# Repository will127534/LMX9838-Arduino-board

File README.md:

# LMX9838-Arduino-board
An Arduino leonardo board with LMX9838 BT2.0 module

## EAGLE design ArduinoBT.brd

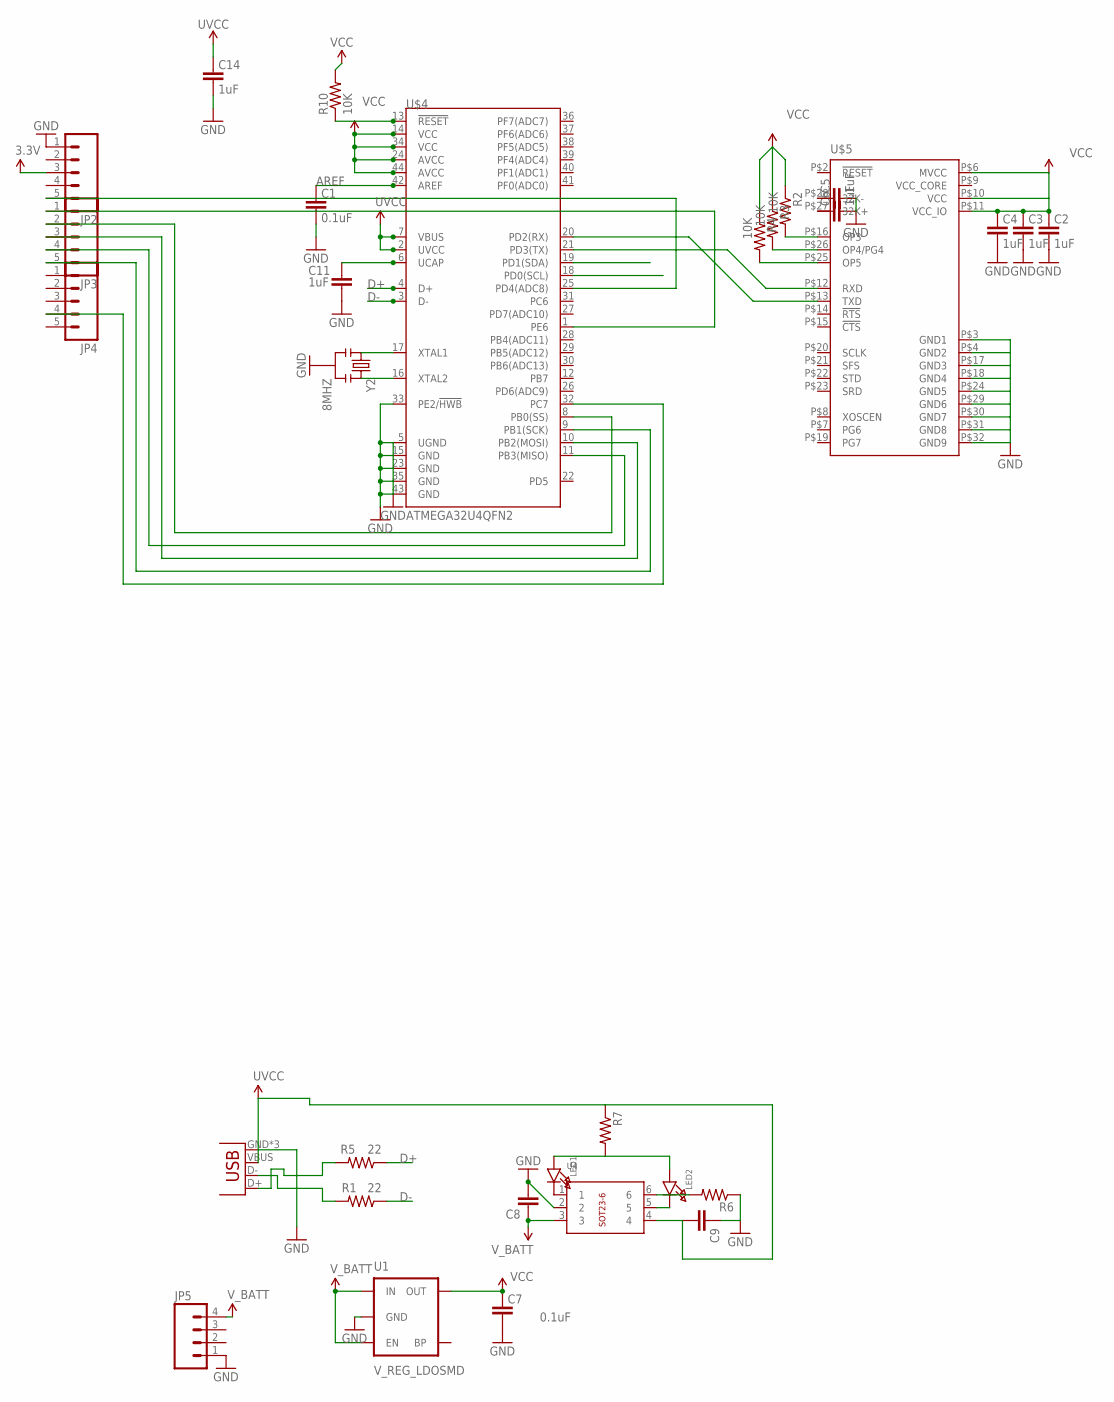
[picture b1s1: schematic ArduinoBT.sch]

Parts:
C1, C7: 0.1uF; 0603-CAP
C2, C3, C4, C5, C6, C11, C14: 1uF; 0603-CAP
C8, C9: CAP0805; 0805
JP1: USB-MICROB
JP2, JP3, JP4: M051.27MM; 1X05-1.27MM
JP5: M041.27MM; 1X04-1.27MM
LED1, LED2: LED0603_NOOUTLINE; CHIPLED_0603_NOOUTLINE
R1, R5: 22; 0603-RES
R2, R3, R4, R10: 10K; 0603-RES
R6, R7: RESISTOR0805-RES; 0805
U1: V_REG_LDOSMD; SOT23-5
U4: BREAKOUT_SOT23-6
U$4: ATMEGA32U4QFN2; SPARKFUN-DIGITALIC_QFN-44-NOPAD
U$5: LMX9838; LTCC70
Y2: 8MHZ; RESONATOR-SMD

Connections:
3.3V: C2.2, C3.2, C4.2, C7.2, JP2.3, R2.1, R3.1, R4.1, R10.2, U1.5 (OUT), U$4.14 (VCC), U$4.24 (AVCC), U$4.34 (VCC), U$4.44 (AVCC), U$5.P$6 (MVCC), U$5.P$10 (VCC), U$5.P$11 (VCC_IO)
AREF: C1.2, U$4.42 (AREF)
D+: R5.1, U$4.4 (D+)
D-: R1.1, U$4.3 (D-)
GND: C1.1, C2.1, C3.1, C4.1, C5.1, C6.1, C7.1, C8.2, C9.1, C11.1, C14.1, JP1.GND, JP1.MT1 (GND), JP1.MT2 (GND), JP2.1, JP5.1, R6.1, U1.2 (GND), U4.2, U$4.5 (UGND), U$4.15 (GND), U$4.23 (GND), U$4.33 (PE2/!HWB), U$4.35 (GND), U$4.43 (GND), U$5.P$3 (GND1), U$5.P$4 (GND2), U$5.P$17 (GND3), U$5.P$18 (GND4), U$5.P$24 (GND5), U$5.P$29 (GND6), U$5.P$30 (GND7), U$5.P$31 (GND8), U$5.P$32 (GND9), Y2.2
unnamed: R2.2, U$5.P$16 (OP3)
unnamed: R3.2, U$5.P$26 (OP4/PG4)
unnamed: C11.2, U$4.6 (UCAP)
unnamed: R4.2, U$5.P$25 (OP5)
unnamed: C5.2, U$5.P$28 (32K-)
unnamed: JP1.D-, R1.2
unnamed: JP1.D+, R5.2
unnamed: C6.2, U$5.P$27 (32K+)
unnamed: U$4.16 (XTAL2), Y2.3
unnamed: R6.2, U4.6
unnamed: JP2.5, U$4.25 (PD4(ADC8))
unnamed: JP3.1, U$4.1 (PE6)
unnamed: JP3.2, U$4.8 (PB0(SS))
unnamed: JP3.3, U$4.10 (PB2(MOSI))
unnamed: JP3.4, U$4.11 (PB3(MISO))
unnamed: JP3.5, U$4.9 (PB1(SCK))
unnamed: U$4.17 (XTAL1), Y2.1
unnamed: LED1.A, LED2.A, R7.2
unnamed: JP4.4, U$4.32 (PC7)
unnamed: R10.1, U$4.13 (!RESET)
unnamed: U$4.20 (PD2(RX)), U$5.P$13 (TXD)
unnamed: U$4.21 (PD3(TX)), U$5.P$12 (RXD)
unnamed: LED1.C, U4.1
unnamed: LED2.C, U4.5
UVCC: C9.2, C14.2, JP1.VBUS, R7.1, U4.4, U$4.2 (UVCC), U$4.7 (VBUS)
VCC_CORE: U$5.P$9 (VCC_CORE)
V_BATT: C8.1, JP5.4, U1.1 (IN), U1.3 (EN), U4.3

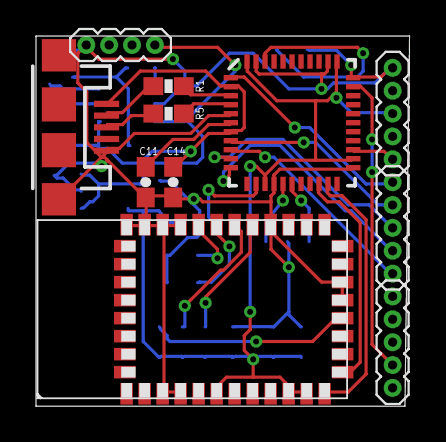
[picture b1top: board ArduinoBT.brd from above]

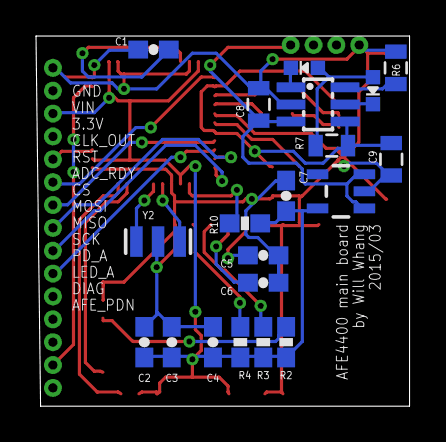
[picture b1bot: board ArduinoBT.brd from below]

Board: 2 copper layers, 20.8 x 20.6 mm, 31 parts (20 on the bottom side), 31 nets.

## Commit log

2015-07-04 Upload PCB files

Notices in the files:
parts and their libraries:
SparkFun-Connectors: Licensing: CC v3.0 Share-Alike You are welcome to use this library for commercial purposes.
microbuilder: This work is placed in the public domain, and may be freely used for commercial and non-commercial work with the following conditions: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
